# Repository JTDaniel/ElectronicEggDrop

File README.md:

# ElectronicEggDrop
This is a project Pioneered by the Arizona State University MakerSpace workers, J. Travis Daniel, Gehrig Dixon, and Liam Nelson.  The goal is to make an egg drop experiment that is more sustainable than the regular use of this experiment in physics classrooms today.  This is being done by replacing regular edible egss with electronic sensor packages designed to look like an egg.

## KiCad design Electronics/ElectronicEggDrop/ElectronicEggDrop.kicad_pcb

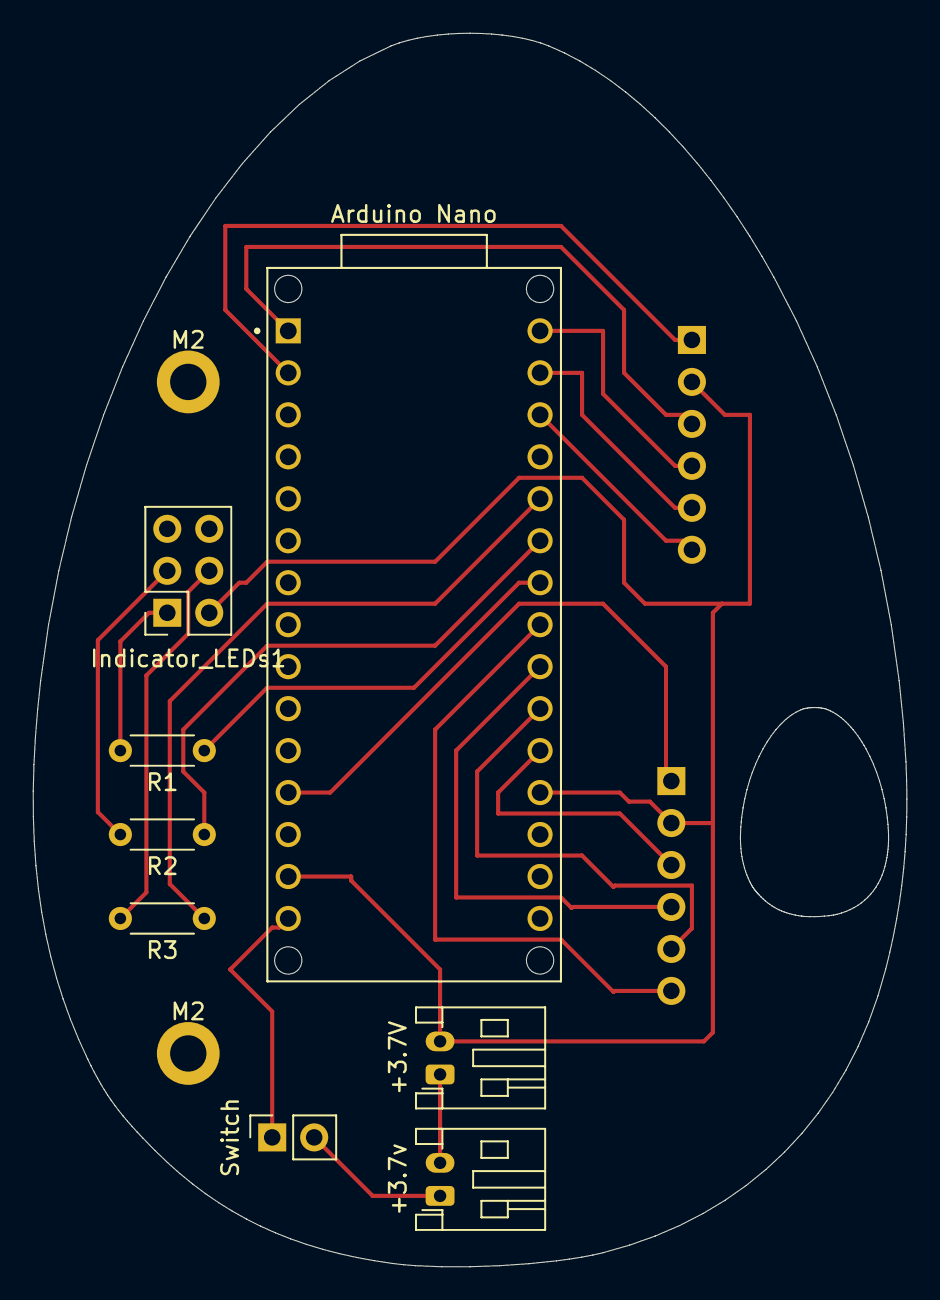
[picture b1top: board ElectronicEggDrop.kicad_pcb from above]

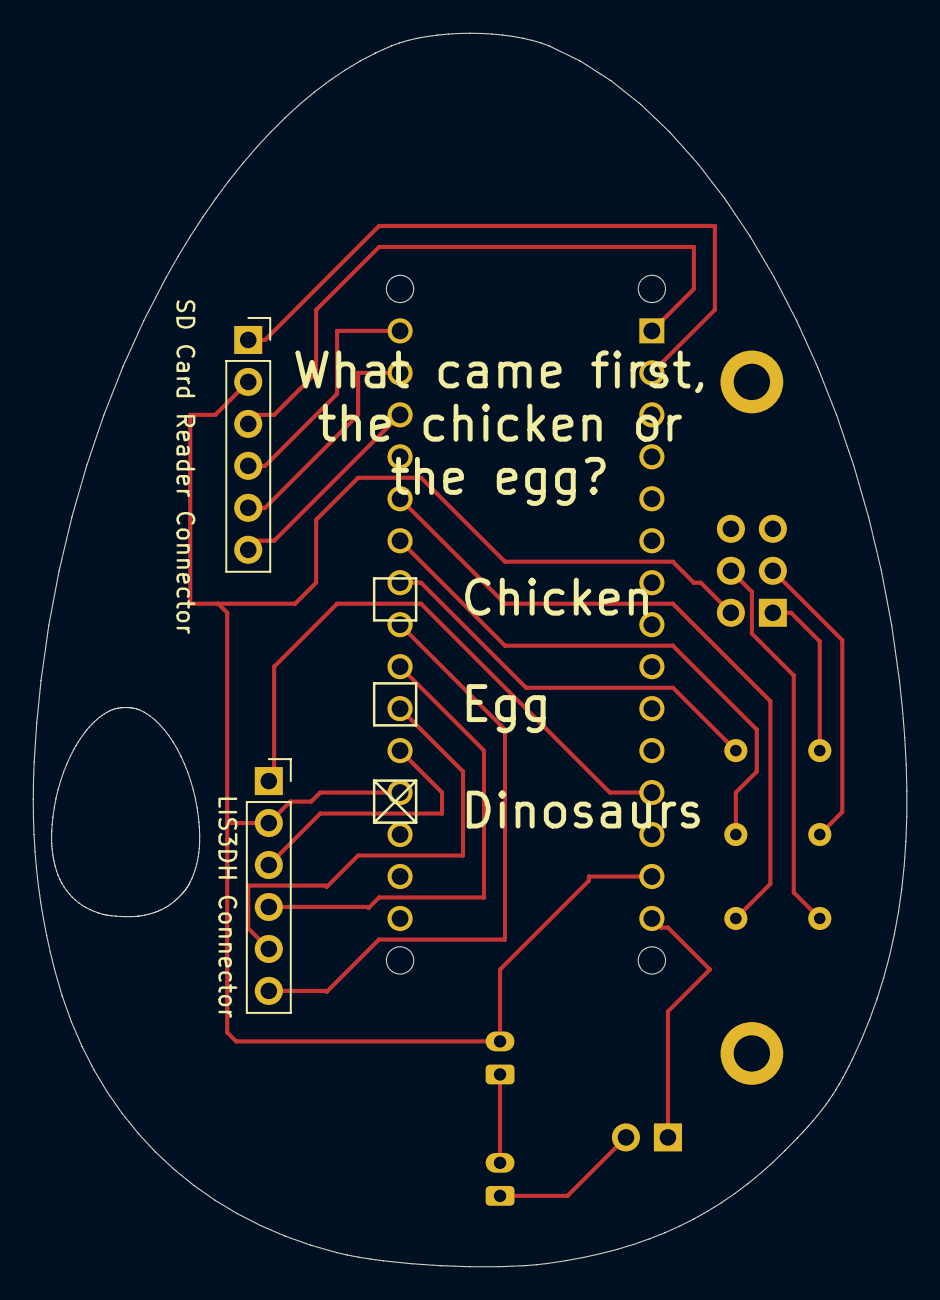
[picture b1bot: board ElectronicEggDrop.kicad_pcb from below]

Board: 2 copper layers, 52.9 x 74.6 mm, 10 parts (2 on the bottom side), 20 nets.

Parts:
+3.7V, +3.7v: Screw_Terminal_01x02; JST_PH_S2B-PH-K_1x02_P2.00mm_Horizontal
Arduino Nano: ABX00053; MODULE_ABX00053
Indicator_LEDs1: LED_RAGB; PinSocket_2x03_P2.54mm_Vertical
LIS3DH Connector: Conn_01x06_Male; PinSocket_1x06_P2.54mm_Vertical
R1, R2, R3: R; R_Axial_DIN0204_L3.6mm_D1.6mm_P5.08mm_Horizontal
SD Card Reader Connector: Conn_01x06_Male; PinSocket_1x06_P2.54mm_Vertical
Switch: SW_SPST; PinSocket_1x02_P2.54mm_Vertical

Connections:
GND: +3.7V.2, Arduino Nano.14 (GND), Arduino Nano.19 (GND), Indicator_LEDs1.2 (A), LIS3DH Connector.2, SD Card Reader Connector.2
unnamed: Arduino Nano.1 (D13/GPIO6), SD Card Reader Connector.3
unnamed: Arduino Nano.2 (+3V3), SD Card Reader Connector.1
unnamed: Arduino Nano.12 (+5V), LIS3DH Connector.1
unnamed: Arduino Nano.15 (VIN), Switch.1 (A)
unnamed: Arduino Nano.20 (D2/GPIO25), LIS3DH Connector.3
unnamed: Arduino Nano.21 (D3/GPIO15), LIS3DH Connector.5
unnamed: Arduino Nano.22 (D4/GPIO26), LIS3DH Connector.4
unnamed: Arduino Nano.23 (D5/GPIO17), LIS3DH Connector.6
unnamed: Arduino Nano.24 (D6/GPIO18), R1.1
unnamed: Arduino Nano.25 (D7/GPIO19), R2.1
unnamed: Arduino Nano.26 (D8/GPIO20), R3.1
unnamed: Arduino Nano.28 (D10/GPIO5), SD Card Reader Connector.6
unnamed: Arduino Nano.29 (D11/GPIO7/COPI), SD Card Reader Connector.5
unnamed: Arduino Nano.30 (D12/GPIO4/CIPO), SD Card Reader Connector.4
unnamed: Indicator_LEDs1.1 (RK), R1.2
unnamed: Indicator_LEDs1.3 (GK), R2.2
unnamed: Indicator_LEDs1.4 (BK), R3.2
unnamed: +3.7v.1, Switch.2 (B)
unnamed: +3.7V.1, +3.7v.2

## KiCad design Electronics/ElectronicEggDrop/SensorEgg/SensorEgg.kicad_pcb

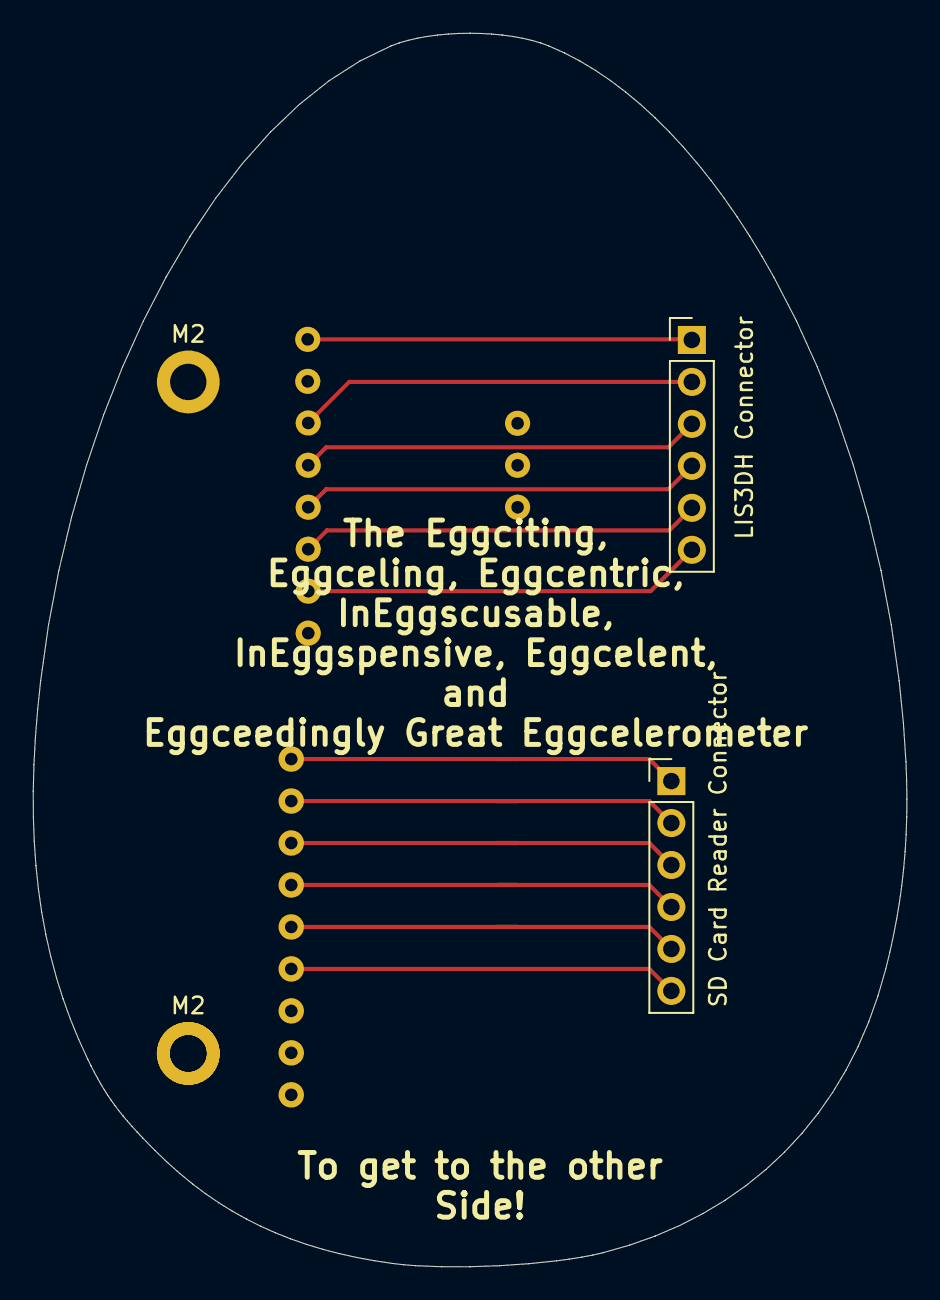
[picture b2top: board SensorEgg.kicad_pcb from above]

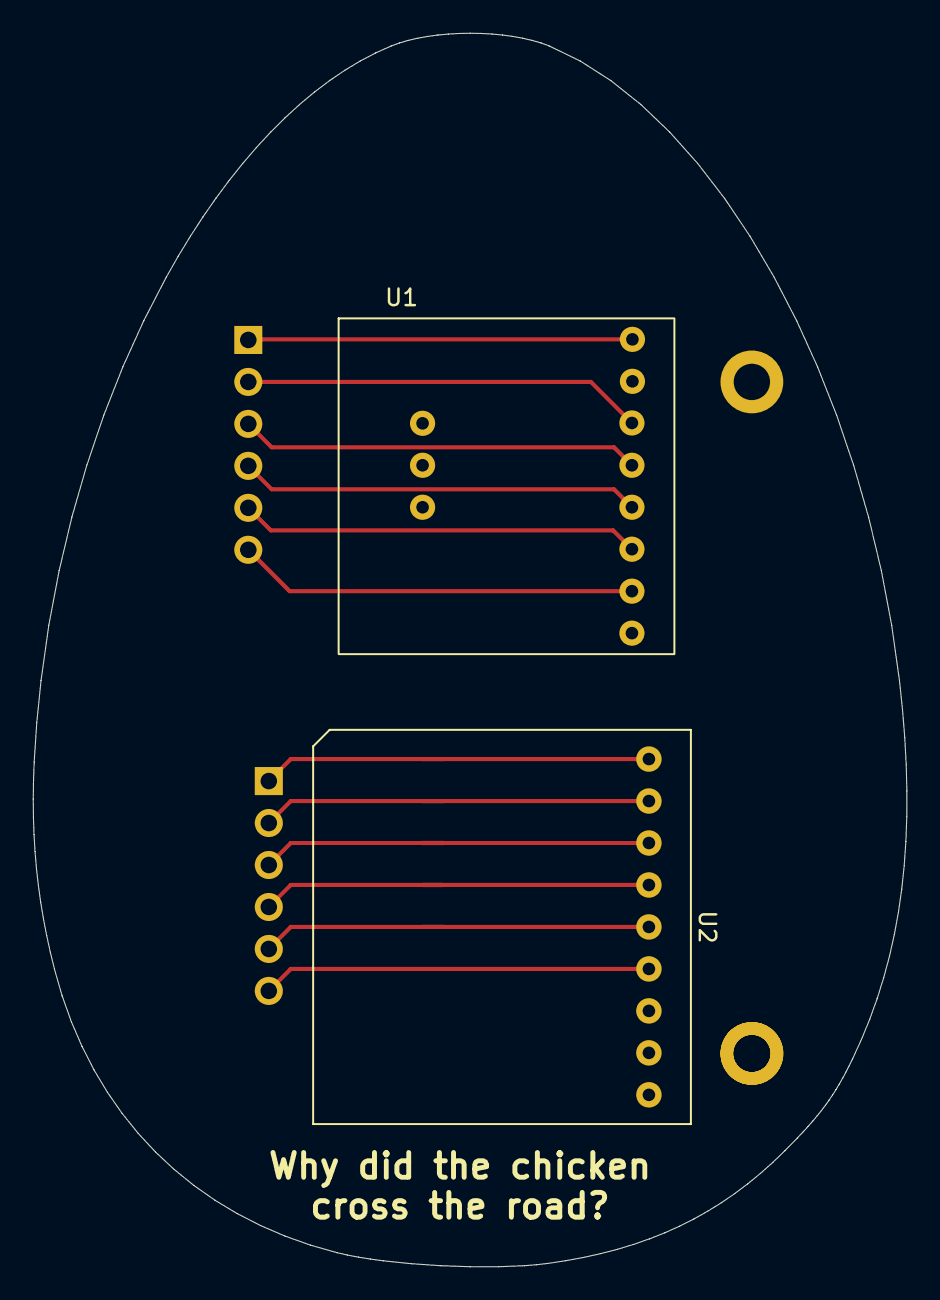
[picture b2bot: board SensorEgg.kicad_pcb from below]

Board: 2 copper layers, 52.9 x 74.6 mm, 6 parts (2 on the bottom side), 12 nets.

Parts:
LIS3DH Connector: Conn_01x06; PinHeader_1x06_P2.54mm_Vertical
M2, M2#2: MountingHole_2.2mm_M2_DIN965_Pad
SD Card Reader Connector: Conn_01x06; PinHeader_1x06_P2.54mm_Vertical
U1: LIS3DH
U2: SDCardReader

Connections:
unnamed: LIS3DH Connector.1, U1.1 (Vin)
unnamed: LIS3DH Connector.2, U1.3 (GND)
unnamed: LIS3DH Connector.3, U1.4 (SCL)
unnamed: LIS3DH Connector.4, U1.5 (SDA)
unnamed: LIS3DH Connector.5, U1.6 (SDO)
unnamed: LIS3DH Connector.6, U1.7 (CS)
unnamed: SD Card Reader Connector.1, U2.1 (3V)
unnamed: SD Card Reader Connector.2, U2.2 (GND)
unnamed: SD Card Reader Connector.3, U2.3 (CLK)
unnamed: SD Card Reader Connector.4, U2.4 (D0/SO)
unnamed: SD Card Reader Connector.5, U2.5 (CMD/SI)
unnamed: SD Card Reader Connector.6, U2.6 (D3/CS)

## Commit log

2022-07-01 Moved Files around, added Arduino folder and SD library to folder.
2022-07-01 Moved Stuff around and added SD library
2022-07-01 added Arduino Main.ino
2022-07-08 Added Accelerometer Library and organized into library folder.
2022-07-08 borked last commit
2022-07-12 Updated Main file with SD card and Accelerometer information. It is set to a 30 second Read/Write timer. Pins for LEDs have been initialized and declared but are not yet implemented.
2022-07-12 Made edits to Main.ino, added in single tap detection, LED commands, and resultant acceleration calculations. Thresholds still need adjusting (Crack and Tap), break from infinite logging loop needs w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
2022-07-13 Edited some code, Created schematic for egg main board
2022-07-13 Created Egg Main board, needs different power connector. Needs secondary board
2022-07-13 added LIS3DH
2022-07-15 Finished V1 of the Control and Sensor Egg boards, 3D models created by FreeCAD. Need to fix code, assemble boards in FreeCAD, and create 3D printed housing
2022-07-15 added STEP of board
2022-07-15 added STL models
2022-07-15 Started Assembly of boards, added Arduino nano and LIS3dh Boards, found new footprints for LIS3DH and SDreader, need to implement them.
2022-07-20 Finished the PCBs
2022-07-20 Added Gerber Files
2022-07-21 Finished V1 of boards, sent them out for manufacturing, BOM genereated but needs editing.
2022-08-11 Created an Egg V2, Version one SensorEgg PCB did not work due to flipped footprints. V2 will be a singal board.
2022-08-19 Updated v2, pretty much ready t order. May experiment with reducing amountof spi wires used.
